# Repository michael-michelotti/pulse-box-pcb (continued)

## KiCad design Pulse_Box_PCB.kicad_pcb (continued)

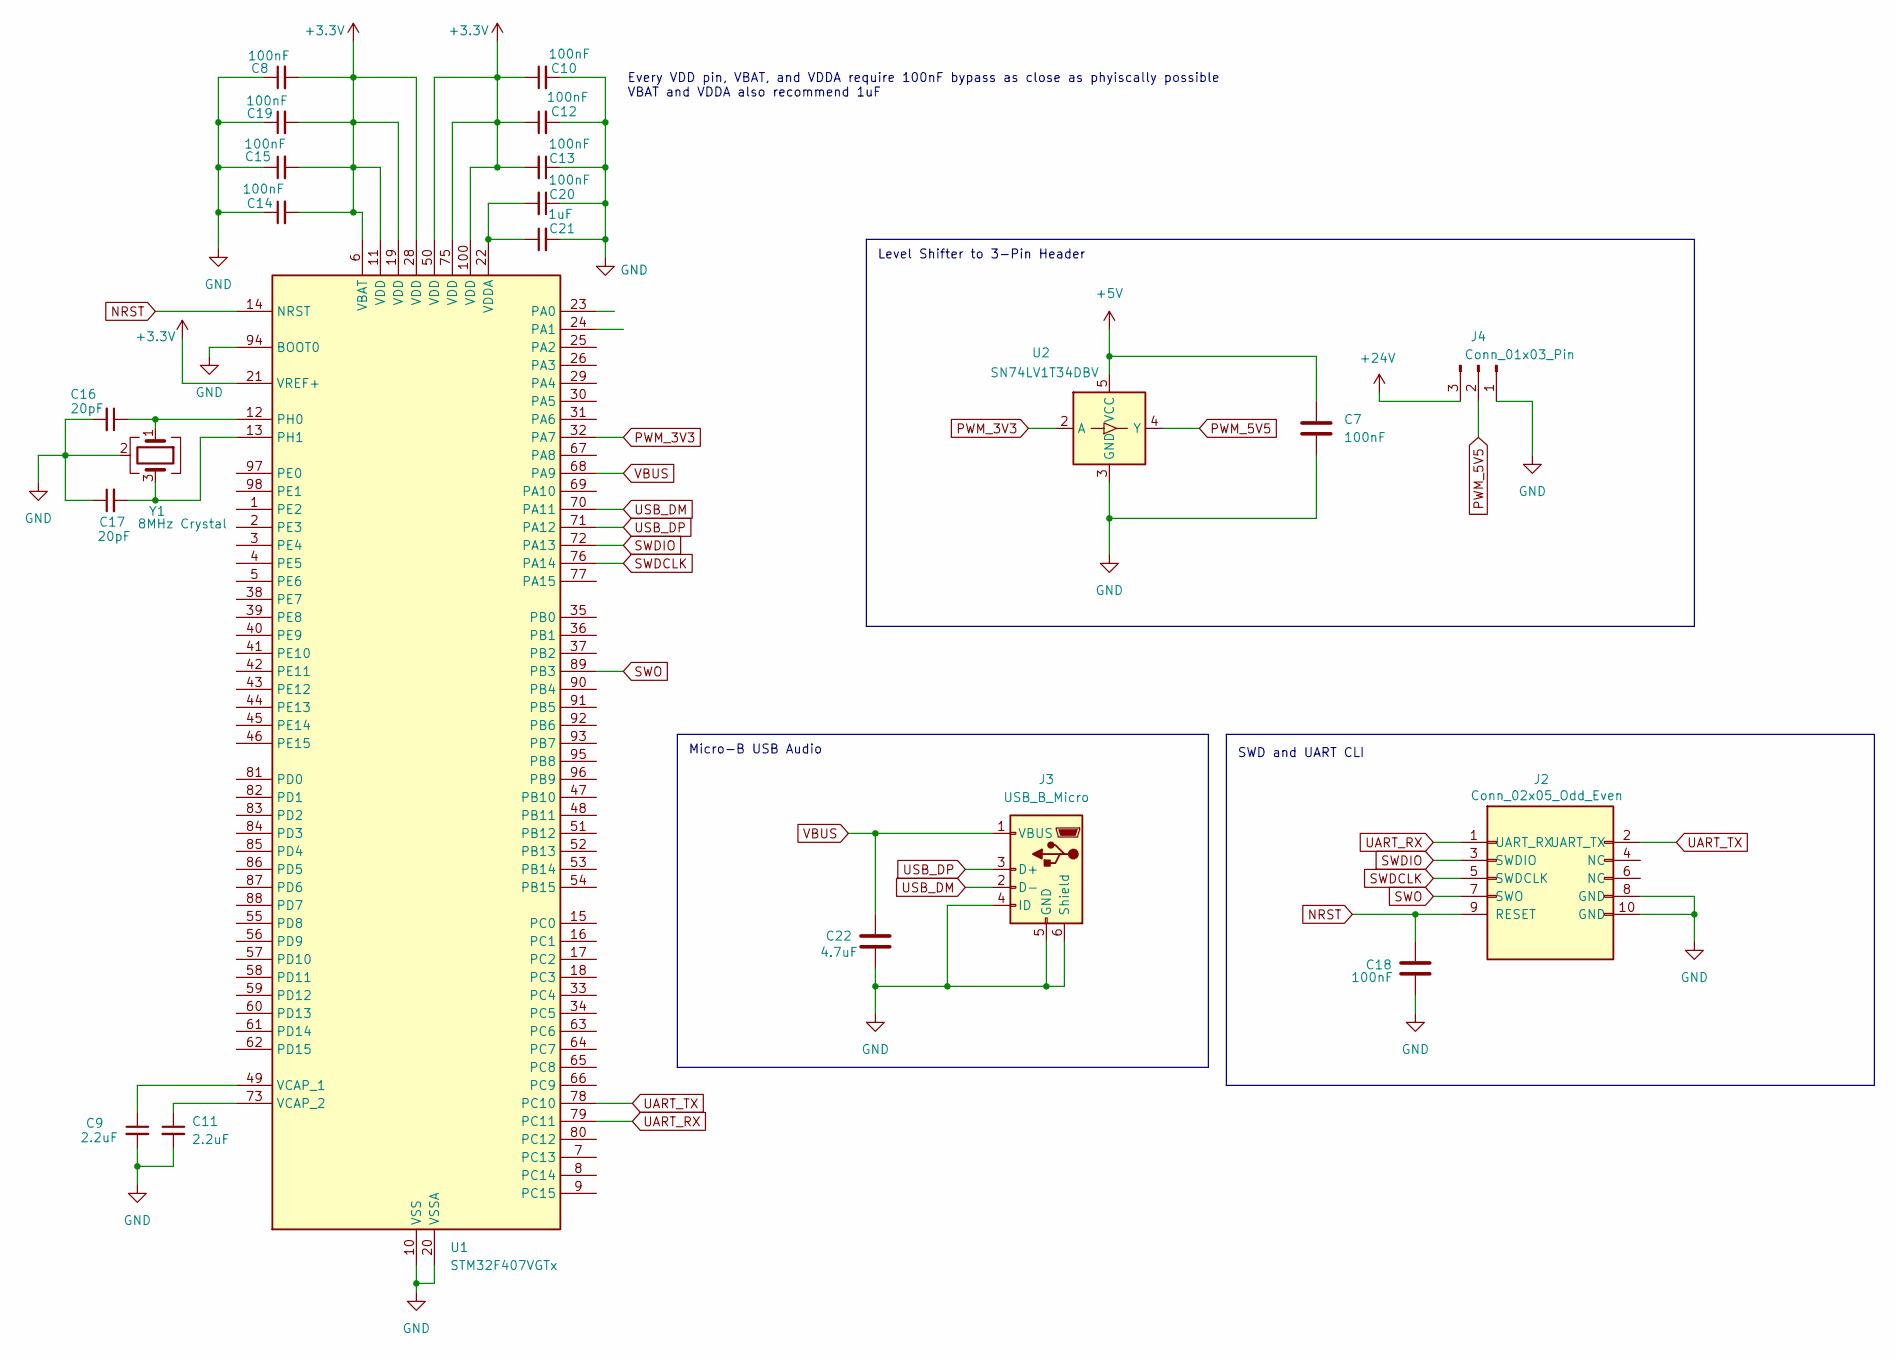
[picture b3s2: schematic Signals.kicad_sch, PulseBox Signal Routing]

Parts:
C7, C8, C10, C12, C13, C14, C15, C18, C19, C20: 100nF; C_0402_1005Metric; MFR PN CL05B104KO5NNNC; JLCPCB PN C1525
C9, C11: 2.2uF; C_0603_1608Metric; MFR PN CL10A225KO8NNNC; JLCPCB PN C23630
C16, C17: 20pF; C_0402_1005Metric; MFR PN 0402CG200J500NT; JLCPCB PN C1554
C21: 1uF; C_0402_1005Metric; MFR PN CL05A105KA5NQNC; JLCPCB PN C52923
C22: 4.7uF; C_0805_2012Metric; MFR PN CL21A475KAQNNNE; JLCPCB PN C1779
J2: Conn_02x05_Odd_Even; PinHeader_2x05_P1.27mm_Vertical; MFR PN 20021111-00010T4LF; JLCPCB PN C239059
J3: USB_B_Micro; USB_Micro-B_Amphenol_10103594-0001LF_Horizontal; MFR PN 10103594-0001LF; JLCPCB PN C428495
J4: Conn_01x03_Pin; PinHeader_1x03_P2.54mm_Vertical; MFR PN 2.54-1*3PPin; JLCPCB PN C49257
U1: STM32F407VGTx; LQFP-100_14x14mm_P0.5mm; MFR PN STM32F407VGT6; JLCPCB PN C919362
U2: SN74LV1T34DBV; SOT-23-5; MFR PN SN74LV1T34DBV; JLCPCB PN C100024
Y1: 8MHz Crystal; Crystal_SMD_3225-4Pin_3.2x2.5mm; MFR PN 1C208000BC0R; JLCPCB PN C57131

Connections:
+3.3V: C8.2, C10.1, C12.1, C13.2, C14.2, C15.2, C19.2, U1.6 (VBAT), U1.11 (VDD), U1.19 (VDD), U1.21 (VREF+), U1.28 (VDD), U1.50 (VDD), U1.75 (VDD), U1.100 (VDD); also elsewhere on the board
+5V: C7.1, U2.5 (VCC); also elsewhere on the board
+24V: J4.3; also elsewhere on the board
GND: C7.2, C8.1, C9.2, C10.2, C11.2, C12.2, C13.1, C14.1, C15.1, C16.2, C17.1, C18.2, C19.1, C20.1, C21.2, C22.2, J2.8 (GND), J2.10 (GND), J3.4 (ID), J3.5 (GND), J3.6 (Shield), J4.1, U1.10 (VSS), U1.20 (VSSA), U1.27 (VSS), U1.74 (VSS), U1.94 (BOOT0), U1.99 (VSS), U2.3 (GND), Y1.2 (G), Y1.4 (G); also elsewhere on the board
NRST: C18.1, J2.9 (RESET), U1.14 (NRST)
unnamed: C16.1, U1.12 (PH0), Y1.1
unnamed: C17.2, U1.13 (PH1), Y1.3
unnamed: C9.1, U1.49 (VCAP_1)
unnamed: C11.1, U1.73 (VCAP_2)
unnamed: C20.2, C21.1, U1.22 (VDDA)
PWM_3V3: U1.32 (PA7), U2.2 (A)
PWM_5V5: J4.2, U2.4 (Y)
SWDCLK: J2.5 (SWDCLK), U1.76 (PA14)
SWDIO: J2.3 (SWDIO), U1.72 (PA13)
SWO: J2.7 (SWO), U1.89 (PB3)
UART_RX: J2.1 (UART_RX), U1.79 (PC11)
UART_TX: J2.2 (UART_TX), U1.78 (PC10)
USB_DM: J3.2 (D-), U1.70 (PA11)
USB_DP: J3.3 (D+), U1.71 (PA12)
VBUS: C22.1, J3.1 (VBUS), U1.68 (PA9)

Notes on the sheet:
Micro-B USB Audio
Level Shifter to 3-Pin Header
SWD and UART CLI
Every VDD pin, VBAT, and VDDA require 100nF bypass as close as phyiscally possible VBAT and VDDA also recommend 1uF

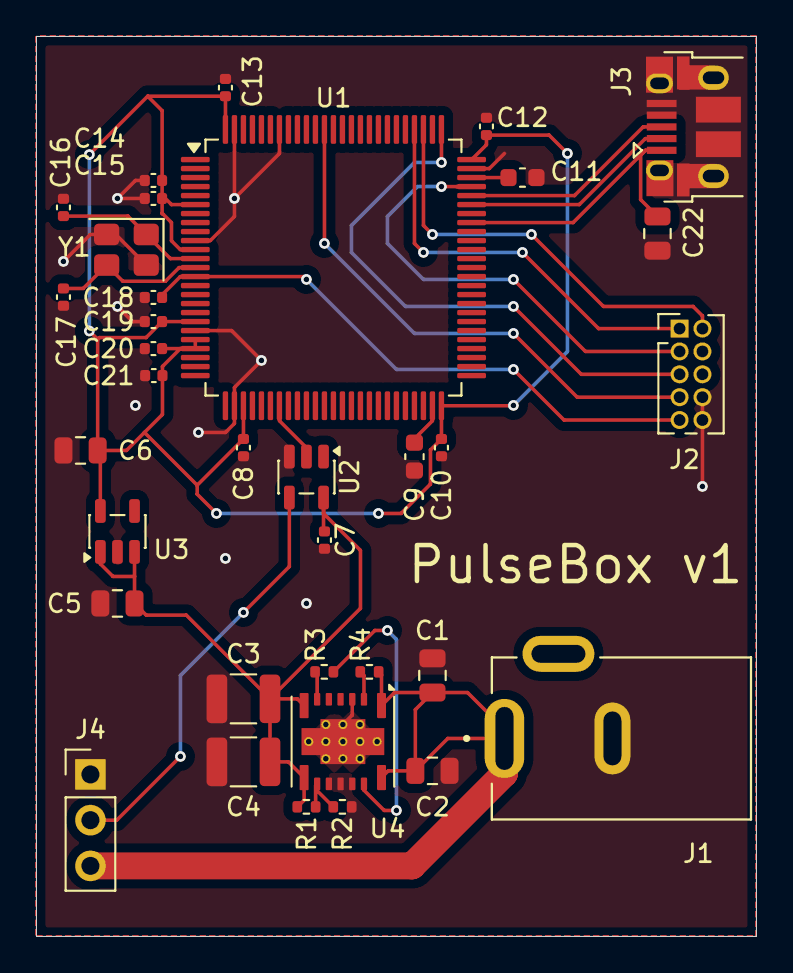
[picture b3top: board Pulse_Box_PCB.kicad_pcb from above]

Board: 2 copper layers, 40.0 x 50.0 mm, 35 parts (0 on the bottom side), 24 nets.

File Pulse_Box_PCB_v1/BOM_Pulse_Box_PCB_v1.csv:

Comment,Designator,Footprint,JLCPCB Part #
10uF,"C1,C2,C5",Capacitor_SMD:C_0805_2012Metric,C15850
47uF,"C3,C4",Capacitor_SMD:C_1210_3225Metric,C77101
4.7uF,"C6,C22",Capacitor_SMD:C_0805_2012Metric,C1779
100nF,"C7,C8,C10,C12,C13,C14,C15,C18,C19,C20",Capacitor_SMD:C_0402_1005Metric,C1525
2.2uF,"C9,C11",Capacitor_SMD:C_0603_1608Metric,C23630
20pF,"C16,C17",Capacitor_SMD:C_0402_1005Metric,C1554
1uF,C21,Capacitor_SMD:C_0402_1005Metric,C52923
Barrel_Jack,J1,Library:XKB_DC-005-5A-2.0,C381116
Conn_02x05_Odd_Even,J2,Connector_PinHeader_1.27mm:PinHeader_2x05_P1.27mm_Vertical,C239059
USB_B_Micro,J3,Connector_USB:USB_Micro-B_Amphenol_10103594-0001LF_Horizontal,C428495
Conn_01x03_Pin,J4,Connector_PinHeader_2.54mm:PinHeader_1x03_P2.54mm_Vertical,C49257
10k,R1,Resistor_SMD:R_0402_1005Metric,C25744
2.37k,R2,Resistor_SMD:R_0402_1005Metric,C294439
100k,"R3,R4",Resistor_SMD:R_0402_1005Metric,C25741
STM32F407VGTx,U1,Package_QFP:LQFP-100_14x14mm_P0.5mm,C919362
SN74LV1T34DBV,U2,Package_TO_SOT_SMD:SOT-23-5,C100024
AP2112K-3.3,U3,Package_TO_SOT_SMD:SOT-23-5,C23380830
TPSM53604RDA,U4,Package_DFN_QFN:Texas_B3QFN-14-1EP_5x5.5mm_P0.65mm_ThermalVia,C2868001
8MHz Crystal,Y1,Crystal:Crystal_SMD_3225-4Pin_3.2x2.5mm,C57131

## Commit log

2026-02-16 initial commit with all kicad files for v1 pcb
2026-02-16 organize schematic into power and signal pages, fixed wire nests
2026-02-28 add v2 board design with esp32-s3 wroom module, moved versions into dedicated directories
2026-03-10 add design for pulsebox panel, update v2 PCB to remove 485 trans
2026-03-12 v2 board mirrored layout
2026-03-14 complete v2 and v1 panel design, this is the final design sent to jlcpcb for v2
2026-04-23 basic readme with board summaries
2026-04-23 upload board images to github, update readme
